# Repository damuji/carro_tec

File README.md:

# carro_tec
Codigo utilizando dentro de los controladores del carro tec

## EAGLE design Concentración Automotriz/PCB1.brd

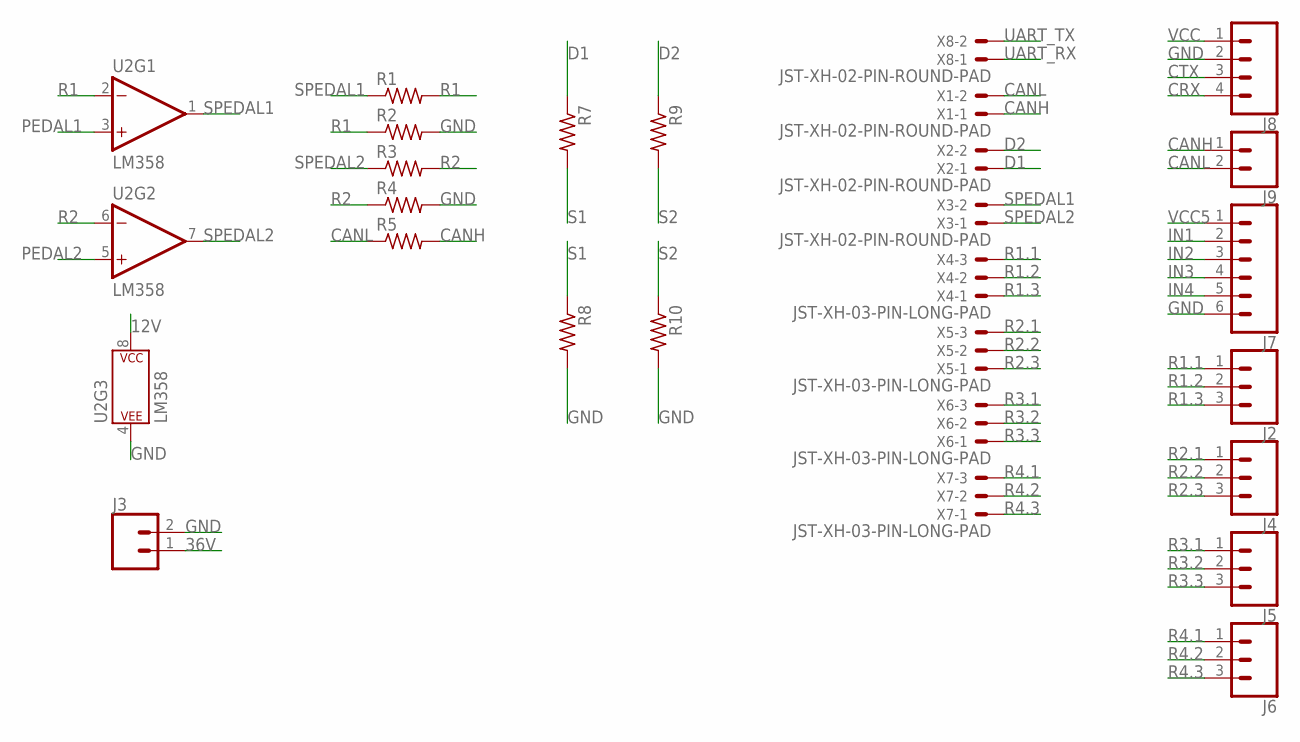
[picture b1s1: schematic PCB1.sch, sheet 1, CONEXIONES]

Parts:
J2, J4, J5, J6: CONN_03; 1X03
J3: CONN_025MM; SCREWTERMINAL-5MM-2
J7: CONN_06SILK_FEMALE_PTH; 1X06
J8: CONN_04; 1X04
J9: CONN_02; 1X02
R1, R2, R3, R4, R5, R7, R8, R9, R10: R-US_0207/10; 0207/10
U2: LM358; DIP08
X1, X2, X3, X8: JST-XH-02-PIN-ROUND-PAD; JST-XH-02-PACKAGE-ROUND-PAD
X4, X5, X6, X7: JST-XH-03-PIN-LONG-PAD; JST-XH-03-PACKAGE-LONG-PAD

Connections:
12V: U2.8 (P$V+); also elsewhere on the board
36V: J3.1; also elsewhere on the board
CANH: J9.1, R5.2, X1.1
CANL: J9.2, R5.1, X1.2
CRX: J8.4; also elsewhere on the board
CTX: J8.3; also elsewhere on the board
D1: R7.1, X2.1
D2: R9.1, X2.2
GND: J3.2, J7.6, J8.2, R2.2, R4.2, R8.2, R10.2, U2.4 (P$V-); also elsewhere on the board
IN1: J7.2; also elsewhere on the board
IN2: J7.3; also elsewhere on the board
IN3: J7.4; also elsewhere on the board
IN4: J7.5; also elsewhere on the board
PEDAL1: U2.3 (+IN); also elsewhere on the board
PEDAL2: U2.5 (+IN); also elsewhere on the board
R1: R1.2, R2.1, U2.2 (-IN)
R1.1: J2.1, X4.3
R1.2: J2.2, X4.2
R1.3: J2.3, X4.1
R2: R3.2, R4.1, U2.6 (-IN)
R2.1: J4.1, X5.3
R2.2: J4.2, X5.2
R2.3: J4.3, X5.1
R3.1: J5.1, X6.3
R3.2: J5.2, X6.2
R3.3: J5.3, X6.1
R4.1: J6.1, X7.3
R4.2: J6.2, X7.2
R4.3: J6.3, X7.1
S1: R7.2, R8.1; also elsewhere on the board
S2: R9.2, R10.1; also elsewhere on the board
SPEDAL1: R1.1, U2.1 (OUT), X3.2
SPEDAL2: R3.1, U2.7 (OUT), X3.1
UART_RX: X8.1; also elsewhere on the board
UART_TX: X8.2; also elsewhere on the board
VCC: J8.1; also elsewhere on the board
VCC5: J7.1; also elsewhere on the board

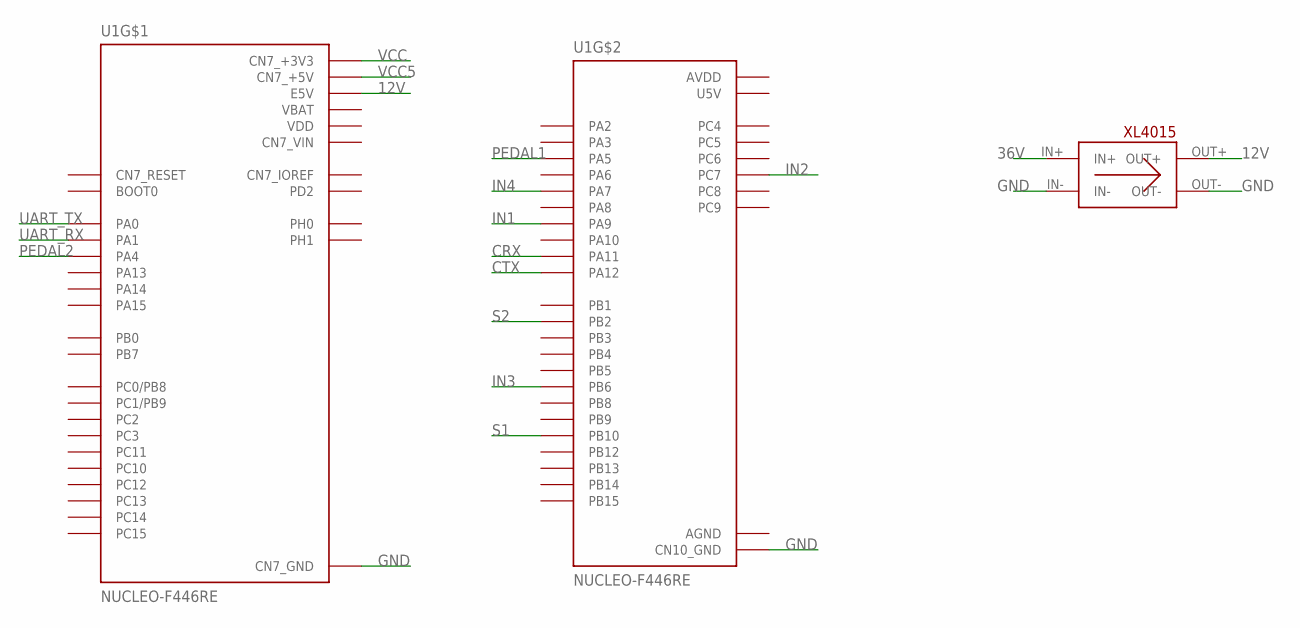
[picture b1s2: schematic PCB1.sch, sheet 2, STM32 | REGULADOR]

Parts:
U1: NUCLEO-F446RE; MODULE_NUCLEO-F446RE
U$4: XL4015

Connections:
12V: U1.CN7_6 (E5V), U$4.OUT+; also elsewhere on the board
36V: U$4.IN+; also elsewhere on the board
AGND: U1.CN10_32 (AGND)
AVDD: U1.CN10_7 (AVDD)
CN7_VIN: U1.CN7_24 (CN7_VIN)
CRX: U1.CN10_14 (PA11); also elsewhere on the board
CTX: U1.CN10_12 (PA12); also elsewhere on the board
GND: U1.CN7_8 (CN7_GND), U1.CN7_19 (CN7_GND), U1.CN7_20 (CN7_GND), U1.CN7_22 (CN7_GND), U1.CN10_9 (CN10_GND), U1.CN10_20 (CN10_GND), U$4.IN-, U$4.OUT-; also elsewhere on the board
IN1: U1.CN10_21 (PA9); also elsewhere on the board
IN2: U1.CN10_19 (PC7); also elsewhere on the board
IN3: U1.CN10_17 (PB6); also elsewhere on the board
IN4: U1.CN10_15 (PA7); also elsewhere on the board
PEDAL1: U1.CN10_11 (PA5); also elsewhere on the board
PEDAL2: U1.CN7_32 (PA4); also elsewhere on the board
S1: U1.CN10_25 (PB10); also elsewhere on the board
S2: U1.CN10_22 (PB2); also elsewhere on the board
U5V: U1.CN10_8 (U5V)
UART_RX: U1.CN7_30 (PA1); also elsewhere on the board
UART_TX: U1.CN7_28 (PA0); also elsewhere on the board
VBAT: U1.CN7_33 (VBAT)
VCC: U1.CN7_16 (CN7_+3V3); also elsewhere on the board
VCC5: U1.CN7_18 (CN7_+5V); also elsewhere on the board
VDD: U1.CN7_5 (VDD)

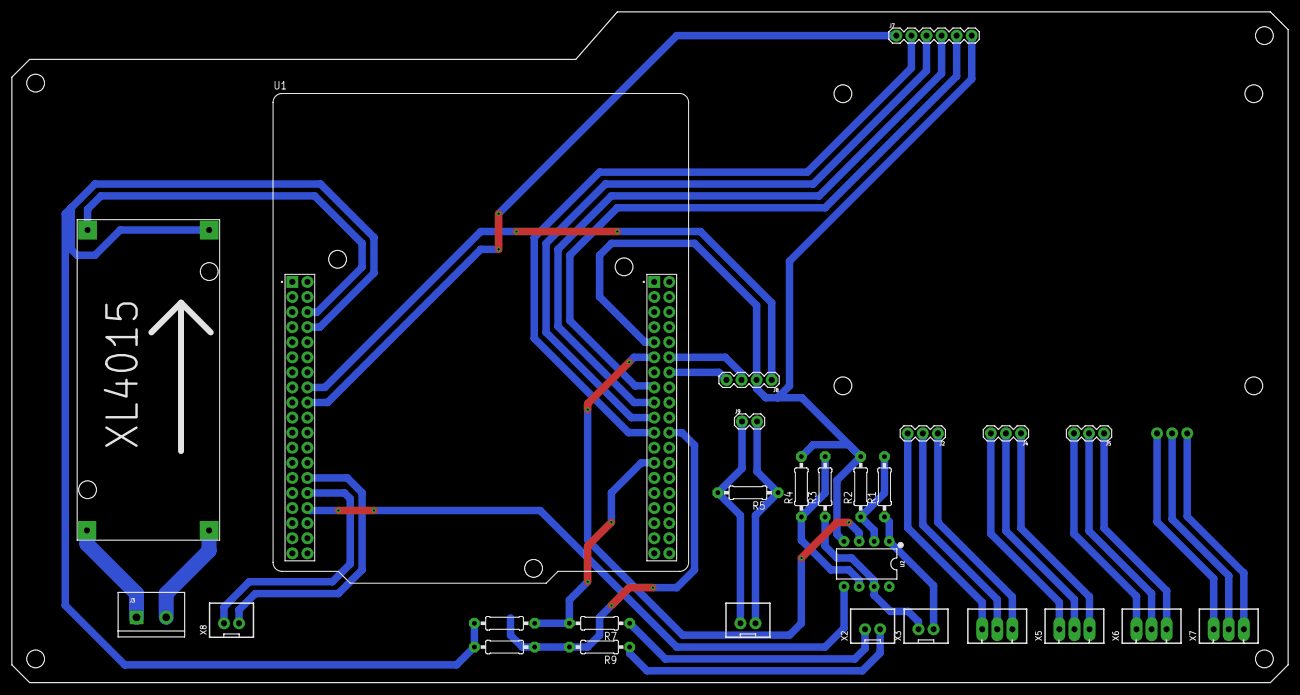
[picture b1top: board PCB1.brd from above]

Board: 2 copper layers, 215.0 x 113.0 mm, 28 parts (1 on the bottom side), 37 nets.

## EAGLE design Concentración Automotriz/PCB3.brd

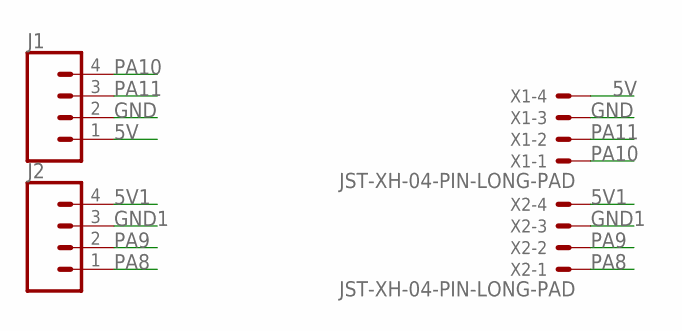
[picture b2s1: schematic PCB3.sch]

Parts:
J1, J2: CONN_04; 1X04
X1, X2: JST-XH-04-PIN-LONG-PAD; JST-XH-04-PACKAGE-LONG-PAD

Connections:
5V: J1.1, X1.4
5V1: J2.4, X2.4
GND: J1.2, X1.3
GND1: J2.3, X2.3
PA8: J2.1, X2.1
PA9: J2.2, X2.2
PA10: J1.4, X1.1
PA11: J1.3, X1.2

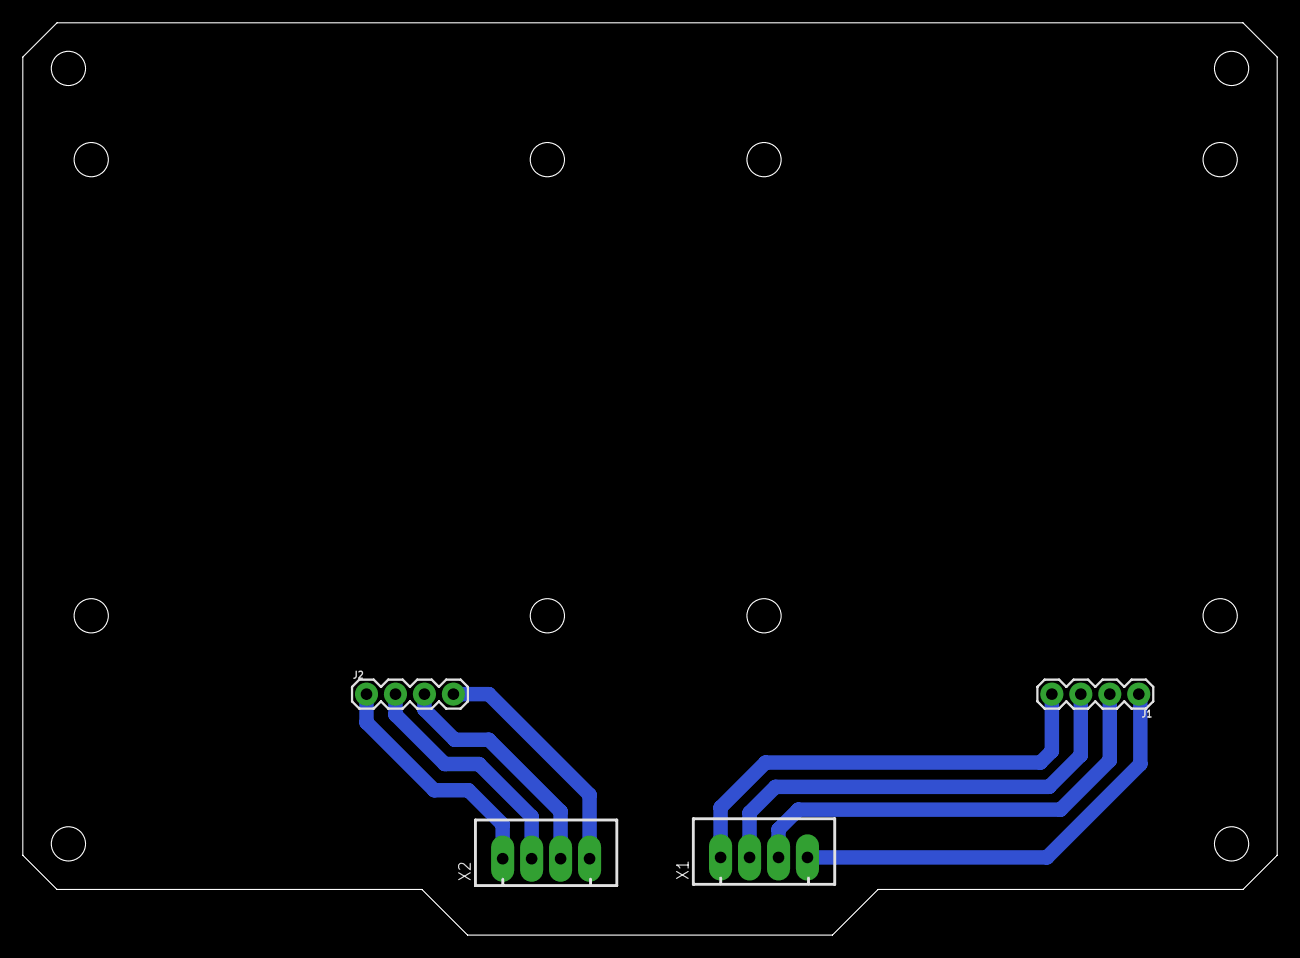
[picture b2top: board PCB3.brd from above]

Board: 2 copper layers, 110.0 x 80.0 mm, 4 parts (0 on the bottom side), 8 nets.

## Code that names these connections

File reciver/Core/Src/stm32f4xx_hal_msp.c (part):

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
    __HAL_RCC_GPIOA_CLK_ENABLE();
    /**ADC1 GPIO Configuration
    PA4     ------> ADC1_IN4
    PA5     ------> ADC1_IN5
    */
    GPIO_InitStruct.Pin = GPIO_PIN_4|GPIO_PIN_5;
    GPIO_InitStruct.Mode = GPIO_MODE_ANALOG;
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
    __HAL_RCC_GPIOA_CLK_ENABLE();
    /**ADC2 GPIO Configuration
    PA4     ------> ADC2_IN4
    */
    GPIO_InitStruct.Pin = GPIO_PIN_4;
    GPIO_InitStruct.Mode = GPIO_MODE_ANALOG;
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    __HAL_RCC_ADC1_CLK_DISABLE();

    /**ADC1 GPIO Configuration
    PA4     ------> ADC1_IN4
    PA5     ------> ADC1_IN5
    */
    HAL_GPIO_DeInit(GPIOA, GPIO_PIN_4|GPIO_PIN_5);

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    __HAL_RCC_ADC2_CLK_DISABLE();

    /**ADC2 GPIO Configuration
    PA4     ------> ADC2_IN4
    */
    HAL_GPIO_DeInit(GPIOA, GPIO_PIN_4);

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
    __HAL_RCC_GPIOB_CLK_ENABLE();
    /**I2C1 GPIO Configuration
    PB6     ------> I2C1_SCL
    PB7     ------> I2C1_SDA
    */
    GPIO_InitStruct.Pin = GPIO_PIN_6|GPIO_PIN_7;
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    __HAL_RCC_I2C1_CLK_DISABLE();

    /**I2C1 GPIO Configuration
    PB6     ------> I2C1_SCL
    PB7     ------> I2C1_SDA
    */
    HAL_GPIO_DeInit(GPIOB, GPIO_PIN_6);
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
    __HAL_RCC_GPIOA_CLK_ENABLE();
    /**TIM2 GPIO Configuration
    PA0-WKUP     ------> TIM2_CH1
    PA1     ------> TIM2_CH2
    */
    GPIO_InitStruct.Pin = GPIO_PIN_0|GPIO_PIN_1;
    GPIO_InitStruct.Mode = GPIO_MODE_AF_PP;
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
    __HAL_RCC_GPIOA_CLK_ENABLE();
    /**TIM1 GPIO Configuration
    PA8     ------> TIM1_CH1
    PA9     ------> TIM1_CH2
    PA10     ------> TIM1_CH3
    PA11     ------> TIM1_CH4
    */
    GPIO_InitStruct.Pin = GPIO_PIN_8|GPIO_PIN_9|GPIO_PIN_10|GPIO_PIN_11;
    GPIO_InitStruct.Mode = GPIO_MODE_AF_PP;
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    __HAL_RCC_TIM2_CLK_DISABLE();

    /**TIM2 GPIO Configuration
    PA0-WKUP     ------> TIM2_CH1
    PA1     ------> TIM2_CH2
    */
    HAL_GPIO_DeInit(GPIOA, GPIO_PIN_0|GPIO_PIN_1);

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
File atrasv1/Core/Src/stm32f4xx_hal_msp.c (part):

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
    __HAL_RCC_GPIOA_CLK_ENABLE();
    /**DAC GPIO Configuration
    PA4     ------> DAC_OUT1
    PA5     ------> DAC_OUT2
    */
    GPIO_InitStruct.Pin = GPIO_PIN_4|GPIO_PIN_5;
    GPIO_InitStruct.Mode = GPIO_MODE_ANALOG;
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    __HAL_RCC_DAC_CLK_DISABLE();

    /**DAC GPIO Configuration
    PA4     ------> DAC_OUT1
    PA5     ------> DAC_OUT2
    */
    HAL_GPIO_DeInit(GPIOA, GPIO_PIN_4|GPIO_PIN_5);

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
    __HAL_RCC_GPIOB_CLK_ENABLE();
    /**TIM2 GPIO Configuration
    PB2     ------> TIM2_CH4
    PB10     ------> TIM2_CH3
    */
    GPIO_InitStruct.Pin = GPIO_PIN_2|GPIO_PIN_10;
    GPIO_InitStruct.Mode = GPIO_MODE_AF_PP;
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    __HAL_RCC_TIM2_CLK_DISABLE();

    /**TIM2 GPIO Configuration
    PB2     ------> TIM2_CH4
    PB10     ------> TIM2_CH3
    */
    HAL_GPIO_DeInit(GPIOB, GPIO_PIN_2|GPIO_PIN_10);

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
    __HAL_RCC_GPIOA_CLK_ENABLE();
    /**UART4 GPIO Configuration
    PA0-WKUP     ------> UART4_TX
    PA1     ------> UART4_RX
    */
    GPIO_InitStruct.Pin = GPIO_PIN_0|GPIO_PIN_1;
    GPIO_InitStruct.Mode = GPIO_MODE_AF_PP;
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    __HAL_RCC_UART4_CLK_DISABLE();

    /**UART4 GPIO Configuration
    PA0-WKUP     ------> UART4_TX
    PA1     ------> UART4_RX
    */
    HAL_GPIO_DeInit(GPIOA, GPIO_PIN_0|GPIO_PIN_1);

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
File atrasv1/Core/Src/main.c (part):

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  /*Configure GPIO pin Output Level */
  HAL_GPIO_WritePin(GPIOB, GPIO_PIN_6, GPIO_PIN_SET);

  /*Configure GPIO pins : PA7 PA9 */
  GPIO_InitStruct.Pin = GPIO_PIN_7|GPIO_PIN_9;
  GPIO_InitStruct.Mode = GPIO_MODE_OUTPUT_PP;
  GPIO_InitStruct.Pull = GPIO_NOPULL;
  GPIO_InitStruct.Speed = GPIO_SPEED_FREQ_LOW;
  HAL_GPIO_Init(GPIOA, &GPIO_InitStruct);

  /*Configure GPIO pin : PC7 */
  GPIO_InitStruct.Pin = GPIO_PIN_7;
  GPIO_InitStruct.Mode = GPIO_MODE_OUTPUT_PP;
  GPIO_InitStruct.Pull = GPIO_NOPULL;
  GPIO_InitStruct.Speed = GPIO_SPEED_FREQ_LOW;
  HAL_GPIO_Init(GPIOC, &GPIO_InitStruct);

  /*Configure GPIO pin : PB6 */
  GPIO_InitStruct.Pin = GPIO_PIN_6;
  GPIO_InitStruct.Mode = GPIO_MODE_OUTPUT_PP;
  GPIO_InitStruct.Pull = GPIO_NOPULL;
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
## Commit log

2023-09-29 implementacion de la uart
2023-09-29 implementacion del pedal
2023-09-29 sistema de lectura
2023-09-29 ahora el uart esta en una interrupcion
2023-09-29 pequeña optimizacion
2023-10-02 se incluyo el cambio de velocidad
2023-10-02 filtro al pedal
2023-10-05 comentario
2023-11-01 separacion de apps
2023-11-01 se puso la carpeta apps, con las apps requeridas
2023-11-15 mensaje
2023-11-17 no se
2023-11-21 'final'
2023-11-22 ajustes finos
2023-11-29 se agrego lam interfaz visual del carro
2023-11-30 final
2023-12-03 esquematicos

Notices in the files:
atrasv1/Core/Src/main.c:
Copyright (c) 2023 STMicroelectronics.
All rights reserved.
This software is licensed under terms that can be found in the LICENSE file
parts and their libraries:
Sparkfun_amplifiers: Licensing: Creative Commons ShareAlike 4.0 International - https://creativecommons.org/licenses/by-sa/4.0
